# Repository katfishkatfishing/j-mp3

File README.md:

# J-mp3

<h2>Portable Music Player</h2>

<p align="center">
  
</p>
      <p>Making my own portable music player!</p>
      <p>I recently got interested in making my own electronics, and one day, I saw the Teenage Engineering TP7 field recorder. I loved the design it had, and wanted one. But I checked the price and it was wayy too expensive, so I decided to make my own, just only with the audio playing part and without the cool fancy stuff. I'm very new to this, so I couldn't replicate it very well, pls don't be too harsh on my work lol, but please feel free to give me any advice.</p>
      <p>A portable music player inspired by classic iPods, and trying to match the design style of Teenage Engineering, playing audio directly from an inserted microSD card with support for both high-fidelity analog 3.5mm output and Bluetooth audio streaming.</p>
      <p> ⚡Powered by the <strong>ESP32-S31</strong> and PCM5102A Audio DAC</p>
      <p>More projects and revisions coming soon🙏!</p>
      <p>Note: I know the rotary encoder knob is off and too long, but I temporarily have no solutions for that. 💔</p>

## Capabilities
### Microcontroller & Audio
- **ESP32-S31** (ESP32-S31 embedded, RISC-V 32-bit dual-coremicroprocessor, up to 320 MHz, 2.4 GHz Wi-Fi & Bluetooth 5.4 (LE))
- **PCM5102A** Audio Stereo DAC (32-bit, 384kHz high-resolution audio)
- **TDA1308** Class-AB stereo headphone driver amplifier
- **PJ-320B** 3.5mm headphone jack with analog output & Bluetooth audio support

### Display, Controls & Storage
- **1.73" AMOLED Display** (466×466 resolution via high-speed QSPI)
- **EC11E Rotary Encoder** with integrated push button for scroll navigation
- **MicroSD Card Socket** (Hirose DM3AT push-push) for onboard music storage

### Power & Battery Management
- **TP4056** Li-Ion battery charging IC with thermistor temperature sensing
- **DW01A + FS8205A** integrated battery protection (overcharge, overdischarge, overcurrent)
- **TPS2121** Power Multiplexer / Ideal Diode Controller (seamless automatic switching between USB-C and battery)
- **TPS61023** Synchronous boost converter & low-noise **RT9080-33** LDO regulators
- Supports 3.7V LiPo battery (705050 3000mAh)
- USB Type-C receptacle for charging and power input

## J-mp3 PCB
### Schematic

## BOM

| Item | Parts | Qty. | Price per lot (USD) | Source |
| :--- | :--- | :--- | :--- | :--- |
| Audio jack female | PJ-320B | 1 | 3.27 | https://www.aliexpress.com/item/1005010463642476.html?spm=a2g0o.productlist.main.1.60817974ZmbdiL&algo_pvid=3c162c60-ca97-44d8-a4ea-9733957078ac&pdp_ext_f=%7B%22order%22%3A%22106%22%2C%22eval%22%3A%221%22%2C%22fromPage%22%3A%22search%22%7D&utparam-url=scene%3Asearch%7Cquery_from%3A%7Cx_object_id%3A1005010463642476%7C_p_origin_prod%3A |
| Dual N-channel MOSFET | FS8205A | 1 | 1.59 | https://www.aliexpress.com/item/1005006375737459.html?spm=a2g0o.productlist.main.1.a0b04c51uTVtAf&algo_pvid=7da07ac5-ba7f-498b-ae78-000138901bd1&pdp_ext_f=%7B%22order%22%3A%22244%22%2C%22eval%22%3A%221%22%2C%22fromPage%22%3A%22search%22%7D&utparam-url=scene%3Asearch%7Cquery_from%3A%7Cx_object_id%3A1005006375737459%7C_p_origin_prod%3A |
| Ideal Diode Controller | TPS2121RUXR | 1 | 2.09 | https://www.aliexpress.com/item/1005010183114644.html?spm=a2g0o.productlist.main.1.3b79VBZzVBZzNw&algo_pvid=9486a3c5-64df-4774-9556-4dae7f705c93&pdp_ext_f=%7B%22order%22%3A%2224%22%2C%22eval%22%3A%221%22%2C%22fromPage%22%3A%22search%22%7D&utparam-url=scene%3Asearch%7Cquery_from%3A%7Cx_object_id%3A1005010183114644%7C_p_origin_prod%3A |
| ESP32 MCU unit | ESP32-S31-WROOM-3 | 1 | 5.00 | https://www.aliexpress.com/item/1005012434557649.html?invitationCode=aWNUM0JlQUVtMVZjRFJ2NUUzd2xwOVE1RklZQWlQWWxPTmxjTXVvbi9hV2VQemFTZUJrNWVWT0s1MU1hdTAyWg&srcSns=sns_Copy&spreadType=socialShare&social_params=6000474898907&bizType=ProductDetail&spreadCode=aWNUM0JlQUVtMVZjRFJ2NUUzd2xwOVE1RklZQWlQWWxPTmxjTXVvbi9hV2VQemFTZUJrNWVWT0s1MU1hdTAyWg&aff_fcid=838605f6547d4cdc84d85aee383cff12-1789809629059-02194-_c4m7gKM3&tt=MG&aff_fsk=_c4m7gKM3&aff_platform=default&sk=_c4m7gKM3&aff_trace_key=838605f6547d4cdc84d85aee383cff12-1789809629059-02194-_c4m7gKM3&shareId=6000474898907&businessType=ProductDetail&platform=AE&terminal_id=1d9dfb3eef574216a2bcb273506f9cd3&afSmartRedirect=y |
| Boost Voltage Converter | TPS61023DRLR | 1 | 0.18 | https://www.aliexpress.com/item/1005008589999406.html?spm=a2g0o.productlist.main.1.7ed1dAWodAWo0a&algo_pvid=7237dc5c-62cd-42a2-a2e9-dc6ba816f7c3&pdp_ext_f=%7B%22order%22%3A%22302%22%2C%22eval%22%3A%221%22%2C%22fromPage%22%3A%22search%22%7D&utparam-url=scene%3Asearch%7Cquery_from%3A%7Cx_object_id%3A1005008589999406%7C_p_origin_prod%3A |
| Ceramic capacitor SMD | 1uF 0402 | 8 | 2.04 | https://www.aliexpress.com/item/1005012364450156.html?spm=a2g0o.productlist.main.1.589f1Ml51Ml5PA&algo_pvid=64ebbb0e-c998-4523-81f0-ca4e95cd79e7&pdp_ext_f=%7B%22order%22%3A%221484%22%2C%22eval%22%3A%221%22%2C%22fromPage%22%3A%22search%22%7D&utparam-url=scene%3Asearch%7Cquery_from%3A%7Cx_object_id%3A1005012364450156%7C_p_origin_prod%3A |
| P-Channel MOSFET | AO3401A | 1 | 1.99 | https://www.aliexpress.com/item/1005008388291353.html?spm=a2g0o.productlist.main.1.25206b4c4LUtde&algo_pvid=8b50fb0f-e682-4ae7-85c1-8edc45618de3&pdp_ext_f=%7B%22order%22%3A%22692%22%2C%22eval%22%3A%221%22%2C%22fromPage%22%3A%22search%22%7D&utparam-url=scene%3Asearch%7Cquery_from%3A%7Cx_object_id%3A1005008388291353%7C_p_origin_prod%3A |
| Diode | 1N4148 | 2 | 1.97 | https://www.aliexpress.com/item/1005007160563285.html?spm=a2g0o.productlist.main.5.49757952BcmT3Y&algo_pvid=de4616c8-ec89-4be4-9121-617d58f16258&pdp_ext_f=%7B%22order%22%3A%222068%22%2C%22spu_best_type%22%3A%22price%22%2C%22eval%22%3A%221%22%2C%22fromPage%22%3A%22search%22%7D&utparam-url=scene%3Asearch%7Cquery_from%3A%7Cx_object_id%3A1005007160563285%7C_p_origin_prod%3A |
| Audio Stereo DAC | PCM5102A | 1 | 4.46 | https://www.aliexpress.com/item/1005006267865363.html?spm=a2g0o.detail.pcDetailTopMoreOtherSeller.5.308ezYUgzYUgEv&gps-id=pcDetailTopMoreOtherSeller&scm=1007.40050.354490.0&scm_id=1007.40050.354490.0&scm-url=1007.40050.354490.0&pvid=3709ad84-1f45-4f2f-a9d4-9019da4e1276&_t=gps-id%3ApcDetailTopMoreOtherSeller%2Cscm-url%3A1007.40050.354490.0%2Cpvid%3A3709ad84-1f45-4f2f-a9d4-9019da4e1276%2Ctpp_buckets%3A668%232846%238116%232002&pdp_ext_f=%7B%22order%22%3A%2250%22%2C%22eval%22%3A%221%22%2C%22sceneId%22%3A%2230050%22%2C%22fromPage%22%3A%22recommend%22%7D&utparam-url=scene%3ApcDetailTopMoreOtherSeller%7Cquery_from%3A%7Cx_object_id%3A1005006267865363%7C_p_origin_prod%3A |
| Headphone Driver Amplifier | TDA1308 | 1 | 2.08 | https://www.aliexpress.com/item/33051574290.html?spm=a2g0o.productlist.main.16.cf5d7988hDu7CF&algo_pvid=2a75b342-aa82-4fe0-941c-90eca8f2c625&pdp_ext_f=%7B%22order%22%3A%2213%22%2C%22eval%22%3A%221%22%2C%22fromPage%22%3A%22search%22%7D&utparam-url=scene%3Asearch%7Cquery_from%3A%7Cx_object_id%3A33051574290%7C_p_origin_prod%3A |
| Bipolar transistor symbol | NPN SOT-23 | 1 | 5.12 | https://www.aliexpress.com/item/1005012628572946.html?spm=a2g0o.productlist.main.1.1d04e8O1e8O1UQ&algo_pvid=8a51f11c-8b8d-4c0b-af60-1e4180ac1a48&pdp_ext_f=%7B%22order%22%3A%2229%22%2C%22eval%22%3A%221%22%2C%22fromPage%22%3A%22search%22%7D&utparam-url=scene%3Asearch%7Cquery_from%3A%7Cx_object_id%3A1005012628572946%7C_p_origin_prod%3A |
| Generic connector, 02x12 | Conn_02x12_Counter_Clockwise | 1 | 1.50 | https://www.aliexpress.com/item/1005007611939409.html |
| Generic connector, 01x04 | Conn_01x04_Pin | 1 | 1.17 | https://www.aliexpress.com/item/1005012793102722.html?spm=a2g0o.productlist.main.12.573ed4KHd4KHjM&aem_p4p_detail=202609190328541006253439417720000081299&algo_pvid=80c6bcb6-eae0-4a64-9e2c-b5b2595232e3&pdp_ext_f=%7B%22order%22%3A%226%22%2C%22eval%22%3A%221%22%2C%22fromPage%22%3A%22search%22%7D&utparam-url=scene%3Asearch%7Cquery_from%3A%7Cx_object_id%3A1005012793102722%7C_p_origin_prod%3A&search_p4p_id=202609190328541006253439417720000081299_3 |
| Inductor SMD | 2.2uH 0603 | 1 | 2.14 | https://www.aliexpress.com/item/1005004840798951.html?spm=a2g0o.productlist.main.1.4afbESaQESaQvr&algo_pvid=e6f9ad16-910b-43de-9ffc-c876db7ab0df&pdp_ext_f=%7B%22order%22%3A%22359%22%2C%22eval%22%3A%221%22%2C%22fromPage%22%3A%22search%22%7D&utparam-url=scene%3Asearch%7Cquery_from%3A%7Cx_object_id%3A1005004840798951%7C_p_origin_prod%3A |
| Linear Voltage Regulator | RT9080-33GJ5 | 2 | 1.53 | https://www.aliexpress.com/item/1005004159688937.html?spm=a2g0o.productlist.main.1.51784d72rSYVqB&algo_pvid=080971bf-6546-4391-82a5-f72f196448dc&pdp_ext_f=%7B%22order%22%3A%2266%22%2C%22eval%22%3A%221%22%2C%22fromPage%22%3A%22search%22%7D&utparam-url=scene%3Asearch%7Cquery_from%3A%7Cx_object_id%3A1005004159688937%7C_p_origin_prod%3A |
| Micro SD Card Socket | Hirose DM3AT-SF-PEJM5 | 1 | 1.20 | https://www.aliexpress.com/item/1005008529231123.html?spm=a2g0o.productlist.main.15.780faIWTaIWTP1&algo_pvid=3f337965-ee0b-478d-a7b6-a5af69d736c1&pdp_ext_f=%7B%22order%22%3A%2225%22%2C%22eval%22%3A%221%22%2C%22fromPage%22%3A%22search%22%7D&utparam-url=scene%3Asearch%7Cquery_from%3A%7Cx_object_id%3A1005008529231123%7C_p_origin_prod%3A |
| Battery protection | DW01A | 1 | 2.54 | https://www.aliexpress.com/item/1005008626342372.html?spm=a2g0o.productlist.main.1.50895bfdtbnlKJ&algo_pvid=237b56ff-402d-4134-ad38-9a508b1e9970&pdp_ext_f=%7B%22order%22%3A%2270%22%2C%22eval%22%3A%221%22%2C%22fromPage%22%3A%22search%22%7D&utparam-url=scene%3Asearch%7Cquery_from%3A%7Cx_object_id%3A1005008626342372%7C_p_origin_prod%3A |
| Capacitor Tantalum SMD | 100uF 3528-12 (Metric) | 1 | 4.05 | https://my.mouser.com/en/ProductDetail/Vishay-Sprague/293D107X9004B2TE3?qs=N31o%252Bt096guiYtrI%2FhDC5g%3D%3D |
| Capacitor Tantalum SMD | 10uF 0603 | 4 | 9.68 | https://www.aliexpress.com/item/1005003344584575.html?spm=a2g0o.productlist.main.1.7884v2Zuv2ZurL&algo_pvid=d34dac6c-7fb3-48c0-9352-0cc876b7f408&pdp_ext_f=%7B%22order%22%3A%2242%22%2C%22eval%22%3A%221%22%2C%22fromPage%22%3A%22search%22%7D&utparam-url=scene%3Asearch%7Cquery_from%3A%7Cx_object_id%3A1005003344584575%7C_p_origin_prod%3A |
| Push button switch | SW-SMD_TC-1101V-C-B-W | 1 | 0.40 | https://item.szlcsc.com/300030.html |
| Push button switch SMD | SW_SPST_B3U-1000P | 2 | 1.46 | https://www.aliexpress.com/item/1005009548875400.html?spm=a2g0o.productlist.main.1.56ebP1y3P1y3Yd&algo_pvid=e205a10a-479c-4a7d-81eb-9951e2930e82&pdp_ext_f=%7B%22order%22%3A%223%22%2C%22eval%22%3A%221%22%2C%22fromPage%22%3A%22search%22%7D&utparam-url=scene%3Asearch%7Cquery_from%3A%7Cx_object_id%3A1005009548875400%7C_p_origin_prod%3A |
| Ceramic resistor SMD | 10k 0805 | 13 | 1.99 | https://www.aliexpress.com/item/1005007183002569.html?spm=a2g0o.productlist.main.1.68b66b95isN6aN&algo_pvid=385a7354-aa7a-4e7f-8ef9-8c0311d953be&pdp_ext_f=%7B%22order%22%3A%2276%22%2C%22eval%22%3A%221%22%2C%22fromPage%22%3A%22search%22%7D&utparam-url=scene%3Asearch%7Cquery_from%3A%7Cx_object_id%3A1005007183002569%7C_p_origin_prod%3A |
| Ceramic resistor SMD | 2k 0603 | 1 | 1.80 | https://www.aliexpress.com/item/1005003529112557.html?spm=a2g0o.productlist.main.7.4aee65557cxcrB&algo_pvid=0d3dc69f-c884-4762-8069-30f583ccfdb1&pdp_ext_f=%7B%22order%22%3A%22476%22%2C%22spu_best_type%22%3A%22price%22%2C%22eval%22%3A%221%22%2C%22fromPage%22%3A%22search%22%7D&utparam-url=scene%3Asearch%7Cquery_from%3A%7Cx_object_id%3A1005003529112557%7C_p_origin_prod%3A |
| Ceramic resistor SMD | 82k 0805 | 1 | 2.03 | https://www.aliexpress.com/item/1005007183002569.html?spm=a2g0o.productlist.main.1.68b66b95isN6aN&algo_pvid=385a7354-aa7a-4e7f-8ef9-8c0311d953be&pdp_ext_f=%7B%22order%22%3A%2276%22%2C%22eval%22%3A%221%22%2C%22fromPage%22%3A%22search%22%7D&utparam-url=scene%3Asearch%7Cquery_from%3A%7Cx_object_id%3A1005007183002569%7C_p_origin_prod%3A |
| Ceramic resistor SMD | 100 0402 | 1 | 1.38 | https://www.aliexpress.com/item/1005003721873929.html?spm=a2g0o.productlist.main.1.29821u3H1u3HkD&algo_pvid=0c4eed70-6ca0-4e08-b34a-7ee8ebfe2859&pdp_ext_f=%7B%22order%22%3A%22285%22%2C%22eval%22%3A%221%22%2C%22fromPage%22%3A%22search%22%7D&utparam-url=scene%3Asearch%7Cquery_from%3A%7Cx_object_id%3A1005003721873929%7C_p_origin_prod%3A |
| Ceramic resistor SMD | 3.9k 0402 | 4 | 1.38 | https://www.aliexpress.com/item/1005003721873929.html?spm=a2g0o.productlist.main.1.29821u3H1u3HkD&algo_pvid=0c4eed70-6ca0-4e08-b34a-7ee8ebfe2859&pdp_ext_f=%7B%22order%22%3A%22285%22%2C%22eval%22%3A%221%22%2C%22fromPage%22%3A%22search%22%7D&utparam-url=scene%3Asearch%7Cquery_from%3A%7Cx_object_id%3A1005003721873929%7C_p_origin_prod%3A |
| Ceramic resistor SMD | 1m 0603 | 1 | 1.48 | https://www.aliexpress.com/item/1005010109041806.html?spm=a2g0o.productlist.main.1.4a12d8mrd8mrat&algo_pvid=af229fc5-fa32-4342-b395-68c0d5cc9c78&pdp_ext_f=%7B%22order%22%3A%22328%22%2C%22spu_best_type%22%3A%22price%22%2C%22eval%22%3A%221%22%2C%22fromPage%22%3A%22search%22%7D&utparam-url=scene%3Asearch%7Cquery_from%3A%7Cx_object_id%3A1005010109041806%7C_p_origin_prod%3A |
| Ceramic resistor SMD | 5k1 0603 | 2 | 1.75 | https://www.aliexpress.com/item/1005003529112557.html?spm=a2g0o.productlist.main.7.4aee65557cxcrB&algo_pvid=0d3dc69f-c884-4762-8069-30f583ccfdb1&pdp_ext_f=%7B%22order%22%3A%22476%22%2C%22spu_best_type%22%3A%22price%22%2C%22eval%22%3A%221%22%2C%22fromPage%22%3A%22search%22%7D&utparam-url=scene%3Asearch%7Cquery_from%3A%7Cx_object_id%3A1005003529112557%7C_p_origin_prod%3A |
| Ceramic resistor SMD | 1k 0402 | 1 | 1.38 | https://www.aliexpress.com/item/1005003721873929.html?spm=a2g0o.productlist.main.1.29821u3H1u3HkD&algo_pvid=0c4eed70-6ca0-4e08-b34a-7ee8ebfe2859&pdp_ext_f=%7B%22order%22%3A%22285%22%2C%22eval%22%3A%221%22%2C%22fromPage%22%3A%22search%22%7D&utparam-url=scene%3Asearch%7Cquery_from%3A%7Cx_object_id%3A1005003721873929%7C_p_origin_prod%3A |
| Ceramic resistor SMD | 100k 0805 | 6 | 2.00 | https://www.aliexpress.com/item/1005007183002569.html?spm=a2g0o.productlist.main.1.68b66b95isN6aN&algo_pvid=385a7354-aa7a-4e7f-8ef9-8c0311d953be&pdp_ext_f=%7B%22order%22%3A%2276%22%2C%22eval%22%3A%221%22%2C%22fromPage%22%3A%22search%22%7D&utparam-url=scene%3Asearch%7Cquery_from%3A%7Cx_object_id%3A1005007183002569%7C_p_origin_prod%3A |
| Ceramic resistor SMD | 4.7k 0805 | 1 | 2.00 | https://www.aliexpress.com/item/1005007183002569.html?spm=a2g0o.productlist.main.1.68b66b95isN6aN&algo_pvid=385a7354-aa7a-4e7f-8ef9-8c0311d953be&pdp_ext_f=%7B%22order%22%3A%2276%22%2C%22eval%22%3A%221%22%2C%22fromPage%22%3A%22search%22%7D&utparam-url=scene%3Asearch%7Cquery_from%3A%7Cx_object_id%3A1005007183002569%7C_p_origin_prod%3A |
| Ceramic resistor SMD | 470 0603 | 2 | 1.80 | https://www.aliexpress.com/item/1005003529112557.html?spm=a2g0o.productlist.main.7.4aee65557cxcrB&algo_pvid=0d3dc69f-c884-4762-8069-30f583ccfdb1&pdp_ext_f=%7B%22order%22%3A%22476%22%2C%22spu_best_type%22%3A%22price%22%2C%22eval%22%3A%221%22%2C%22fromPage%22%3A%22search%22%7D&utparam-url=scene%3Asearch%7Cquery_from%3A%7Cx_object_id%3A1005003529112557%7C_p_origin_prod%3A |
| Ceramic resistor SMD | 43k 0805 | 1 | 2.03 | https://www.aliexpress.com/item/1005007183002569.html?spm=a2g0o.productlist.main.1.68b66b95isN6aN&algo_pvid=385a7354-aa7a-4e7f-8ef9-8c0311d953be&pdp_ext_f=%7B%22order%22%3A%2276%22%2C%22eval%22%3A%221%22%2C%22fromPage%22%3A%22search%22%7D&utparam-url=scene%3Asearch%7Cquery_from%3A%7Cx_object_id%3A1005007183002569%7C_p_origin_prod%3A |
| Ceramic resistor SMD | 732k 0603 | 1 | 2.10 | https://www.aliexpress.com/item/1005005459557840.html?spm=a2g0o.productlist.main.1.552eKaoZKaoZOW&algo_pvid=d5c5bb48-d381-4227-ba1e-46e8d7582c70&pdp_ext_f=%7B%22order%22%3A%2277%22%2C%22eval%22%3A%221%22%2C%22fromPage%22%3A%22search%22%7D&utparam-url=scene%3Asearch%7Cquery_from%3A%7Cx_object_id%3A1005005459557840%7C_p_origin_prod%3A |
| Rotary encoder with switch | EC11E | 1 | 2.94 | https://www.aliexpress.com/item/32976046900.html?spm=a2g0o.detail.pcDetailBottomMoreOtherSeller.13.6474lV6ElV6Evn&gps-id=pcDetailBottomMoreOtherSeller&scm=1007.14452.396806.0&scm_id=1007.14452.396806.0&scm-url=1007.14452.396806.0&pvid=aeb64c1f-7a29-4ad5-933b-e98472c40c59&_t=gps-id%3ApcDetailBottomMoreOtherSeller%2Cscm-url%3A1007.14452.396806.0%2Cpvid%3Aaeb64c1f-7a29-4ad5-933b-e98472c40c59%2Ctpp_buckets%3A668%232846%238116%232002&pdp_ext_f=%7B%22order%22%3A%22547%22%2C%22eval%22%3A%221%22%2C%22sceneId%22%3A%2230050%22%2C%22fromPage%22%3A%22recommend%22%7D&utparam-url=scene%3ApcDetailBottomMoreOtherSeller%7Cquery_from%3A%7Cx_object_id%3A32976046900%7C_p_origin_prod%3A&search_p4p_id=202608180535232983463426697065023539_2 |
| Single-cell battery | 755060 LiPo 3000mAh | 1 | 8.90 | https://www.aliexpress.com/item/1005006259194674.html?spm=a2g0o.productlist.main.2.36fb5dcS5dcSS8&algo_pvid=e5418aaa-c7d1-42cf-949d-d8510645f5cd&pdp_ext_f=%7B%22order%22%3A%22151%22%2C%22eval%22%3A%221%22%2C%22fromPage%22%3A%22search%22%7D&utparam-url=scene%3Asearch%7Cquery_from%3A%7Cx_object_id%3A1005006259194674%7C_p_origin_prod%3A |
| Li-lon Battery Charger | TP4056 | 1 | 0.52 | https://www.aliexpress.com/item/1005005487915175.html?spm=a2g0o.productlist.main.8.4b6058c9uwNrRB&aem_p4p_detail=202609190258166749914128201200000080084&algo_pvid=0f66a318-1b84-45cd-80d0-95d22f5eb897&pdp_ext_f=%7B%22order%22%3A%22255%22%2C%22eval%22%3A%221%22%2C%22fromPage%22%3A%22search%22%7D&utparam-url=scene%3Asearch%7Cquery_from%3A%7Cx_object_id%3A1005005487915175%7C_p_origin_prod%3A&search_p4p_id=202609190258166749914128201200000080084_2 |
| Thermistor | 10k 0402 | 1 | 2.81 | https://www.aliexpress.com/item/1005010466857933.html?spm=a2g0o.productlist.main.2.4fb8w7gbw7gbc4&algo_pvid=0c2c7f04-0061-4f44-94c4-1ea901b197c0&pdp_ext_f=%7B%22order%22%3A%2228%22%2C%22eval%22%3A%221%22%2C%22fromPage%22%3A%22search%22%7D&utparam-url=scene%3Asearch%7Cquery_from%3A%7Cx_object_id%3A1005010466857933%7C_p_origin_prod%3A |
| Ceramic capacitor SMD | 100nF 0603 | 4 | 2.01 | https://www.aliexpress.com/item/1005007660078779.html?spm=a2g0o.productlist.main.1.41ad17afXggjid&algo_pvid=94b82144-0913-4272-a928-8d27b54f2344&pdp_ext_f=%7B%22order%22%3A%22790%22%2C%22spu_best_type%22%3A%22price%22%2C%22eval%22%3A%221%22%2C%22fromPage%22%3A%22search%22%7D&utparam-url=scene%3Asearch%7Cquery_from%3A%7Cx_object_id%3A1005007660078779%7C_p_origin_prod%3A |
| Ceramic capacitor SMD | 10uF 0805 | 5 | 2.64 | https://www.aliexpress.com/item/1005012364450156.html?spm=a2g0o.productlist.main.1.4a92101aYp6fpR&algo_pvid=def9331d-468c-46b6-a7c2-2492d88f5a7b&pdp_ext_f=%7B%22order%22%3A%221484%22%2C%22eval%22%3A%221%22%2C%22fromPage%22%3A%22search%22%7D&utparam-url=scene%3Asearch%7Cquery_from%3A%7Cx_object_id%3A1005012364450156%7C_p_origin_prod%3A |
| Ceramic capacitor SMD | 1uF 0805 | 3 | 2.35 | https://www.aliexpress.com/item/1005012364450156.html?spm=a2g0o.productlist.main.1.4a92101aYp6fpR&algo_pvid=def9331d-468c-46b6-a7c2-2492d88f5a7b&pdp_ext_f=%7B%22order%22%3A%221484%22%2C%22eval%22%3A%221%22%2C%22fromPage%22%3A%22search%22%7D&utparam-url=scene%3Asearch%7Cquery_from%3A%7Cx_object_id%3A1005012364450156%7C_p_origin_prod%3A |
| Ceramic capacitor SMD | 10nF 0603 | 1 | 2.00 | https://www.aliexpress.com/item/1005007660078779.html?spm=a2g0o.productlist.main.1.41ad17afXggjid&algo_pvid=94b82144-0913-4272-a928-8d27b54f2344&pdp_ext_f=%7B%22order%22%3A%22790%22%2C%22spu_best_type%22%3A%22price%22%2C%22eval%22%3A%221%22%2C%22fromPage%22%3A%22search%22%7D&utparam-url=scene%3Asearch%7Cquery_from%3A%7Cx_object_id%3A1005007660078779%7C_p_origin_prod%3A |
| Ceramic capacitor SMD | 22uF 0805 | 3 | 3.55 | https://www.aliexpress.com/item/1005012364450156.html?spm=a2g0o.productlist.main.1.4a92101aYp6fpR&algo_pvid=def9331d-468c-46b6-a7c2-2492d88f5a7b&pdp_ext_f=%7B%22order%22%3A%221484%22%2C%22eval%22%3A%221%22%2C%22fromPage%22%3A%22search%22%7D&utparam-url=scene%3Asearch%7Cquery_from%3A%7Cx_object_id%3A1005012364450156%7C_p_origin_prod%3A |
| Ceramic capacitor SMD | 0.1uF 0805 | 2 | 1.43 | https://www.aliexpress.com/item/1005006142309480.html?spm=a2g0o.productlist.main.2.5b5d23fbK7Es7i&algo_pvid=b69da919-24fd-4e5c-b25c-abccb2827b6a&pdp_ext_f=%7B%22order%22%3A%226337%22%2C%22spu_best_type%22%3A%22price%22%2C%22eval%22%3A%221%22%2C%22fromPage%22%3A%22search%22%7D&utparam-url=scene%3Asearch%7Cquery_from%3A%7Cx_object_id%3A1005006142309480%7C_p_origin_prod%3A |
| Ceramic capacitor SMD | 100uF 0805 | 2 | 13.72 | https://www.aliexpress.com/item/1005005590636993.html?spm=a2g0o.productlist.main.2.258950300kp4f9&algo_pvid=b9072869-1443-4f9f-9d83-403e7e57091f&pdp_ext_f=%7B%22order%22%3A%22357%22%2C%22spu_best_type%22%3A%22price%22%2C%22eval%22%3A%221%22%2C%22fromPage%22%3A%22search%22%7D&utparam-url=scene%3Asearch%7Cquery_from%3A%7Cx_object_id%3A1005005590636993%7C_p_origin_prod%3A |
| Ceramic capacitor SMD | 0.1uF 0201 | 4 | 0.95 | https://www.aliexpress.com/item/1005008499718166.html?spm=a2g0o.productlist.main.3.4f072457BLp6JC&algo_pvid=708b6ba6-6d07-40b3-8c9c-719163e04cda&pdp_ext_f=%7B%22order%22%3A%22397%22%2C%22eval%22%3A%221%22%2C%22fromPage%22%3A%22search%22%7D&utparam-url=scene%3Asearch%7Cquery_from%3A%7Cx_object_id%3A1005008499718166%7C_p_origin_prod%3A |
| Ceramic capacitor SMD | 2.2uF 0603 | 2 | 2.03 | https://www.aliexpress.com/item/1005007660078779.html?spm=a2g0o.productlist.main.1.41ad17afXggjid&algo_pvid=94b82144-0913-4272-a928-8d27b54f2344&pdp_ext_f=%7B%22order%22%3A%22790%22%2C%22spu_best_type%22%3A%22price%22%2C%22eval%22%3A%221%22%2C%22fromPage%22%3A%22search%22%7D&utparam-url=scene%3Asearch%7Cquery_from%3A%7Cx_object_id%3A1005007660078779%7C_p_origin_prod%3A |
| Ceramic capacitor SMD | 1nF 0603 | 1 | 1.98 | https://www.aliexpress.com/item/1005007660078779.html?spm=a2g0o.productlist.main.1.41ad17afXggjid&algo_pvid=94b82144-0913-4272-a928-8d27b54f2344&pdp_ext_f=%7B%22order%22%3A%22790%22%2C%22spu_best_type%22%3A%22price%22%2C%22eval%22%3A%221%22%2C%22fromPage%22%3A%22search%22%7D&utparam-url=scene%3Asearch%7Cquery_from%3A%7Cx_object_id%3A1005007660078779%7C_p_origin_prod%3A |
| Ceramic capacitor SMD | 2.2nF 0805 | 2 | 3.04 | https://www.aliexpress.com/item/33039604868.html?spm=a2g0o.productlist.main.10.3afdzjnrzjnr3Q&algo_pvid=66e61c7f-f79e-40bc-bf5d-0d52052e1876&pdp_ext_f=%7B%22order%22%3A%2258%22%2C%22eval%22%3A%221%22%2C%22fromPage%22%3A%22search%22%7D&utparam-url=scene%3Asearch%7Cquery_from%3A%7Cx_object_id%3A33039604868%7C_p_origin_prod%3A |
| Ceramic capacitor SMD | 100pF 0603 | 1 | 2.03 | https://www.aliexpress.com/item/1005007660078779.html?spm=a2g0o.productlist.main.1.1729LAMPLAMPww&algo_pvid=134453e7-f153-4dc4-9327-eebe4236be4f&pdp_ext_f=%7B%22order%22%3A%22790%22%2C%22spu_best_type%22%3A%22price%22%2C%22eval%22%3A%221%22%2C%22fromPage%22%3A%22search%22%7D&utparam-url=scene%3Asearch%7Cquery_from%3A%7Cx_object_id%3A1005007660078779%7C_p_origin_prod%3A |
| USBType-C Receptacle | USB4125-GF-A | 1 | 0.60 | https://www.digikey.my/en/products/detail/gct/USB4125-GF-A/13547388 |
| AMOLED Display | 1.73 inch 466x466 QSPI | 1 | 7.47 | https://item.taobao.com/item.htm?id=952177467095&mi_id=0000jOy7u6r5ZkyFyRkc3t68ZxdEMGvtNs0QXCuW6-oULvo&spm=a21xtw.29178619.0.0&xxc=shop |
| Total+Shipping+Tax | - | - | 139.55± | - |

### Footprint
<table>
  <tr>
    <td>
      
    </td>
    <td>
      
    </td>
  </tr>
  <tr>
    <td>
      
    </td>
    <td>
      
    </td>
  </tr>
</table>

### 3D View
<table>
  <tr>
    <td>
      
    </td>
    <td>
      
    </td>
  </tr>
  <tr>
    <td>
      
    </td>
    <td>
      
    </td>
  </tr>
  <tr>
    <td>
      
    </td>
    <td>
      
    </td>
  </tr>
</table>

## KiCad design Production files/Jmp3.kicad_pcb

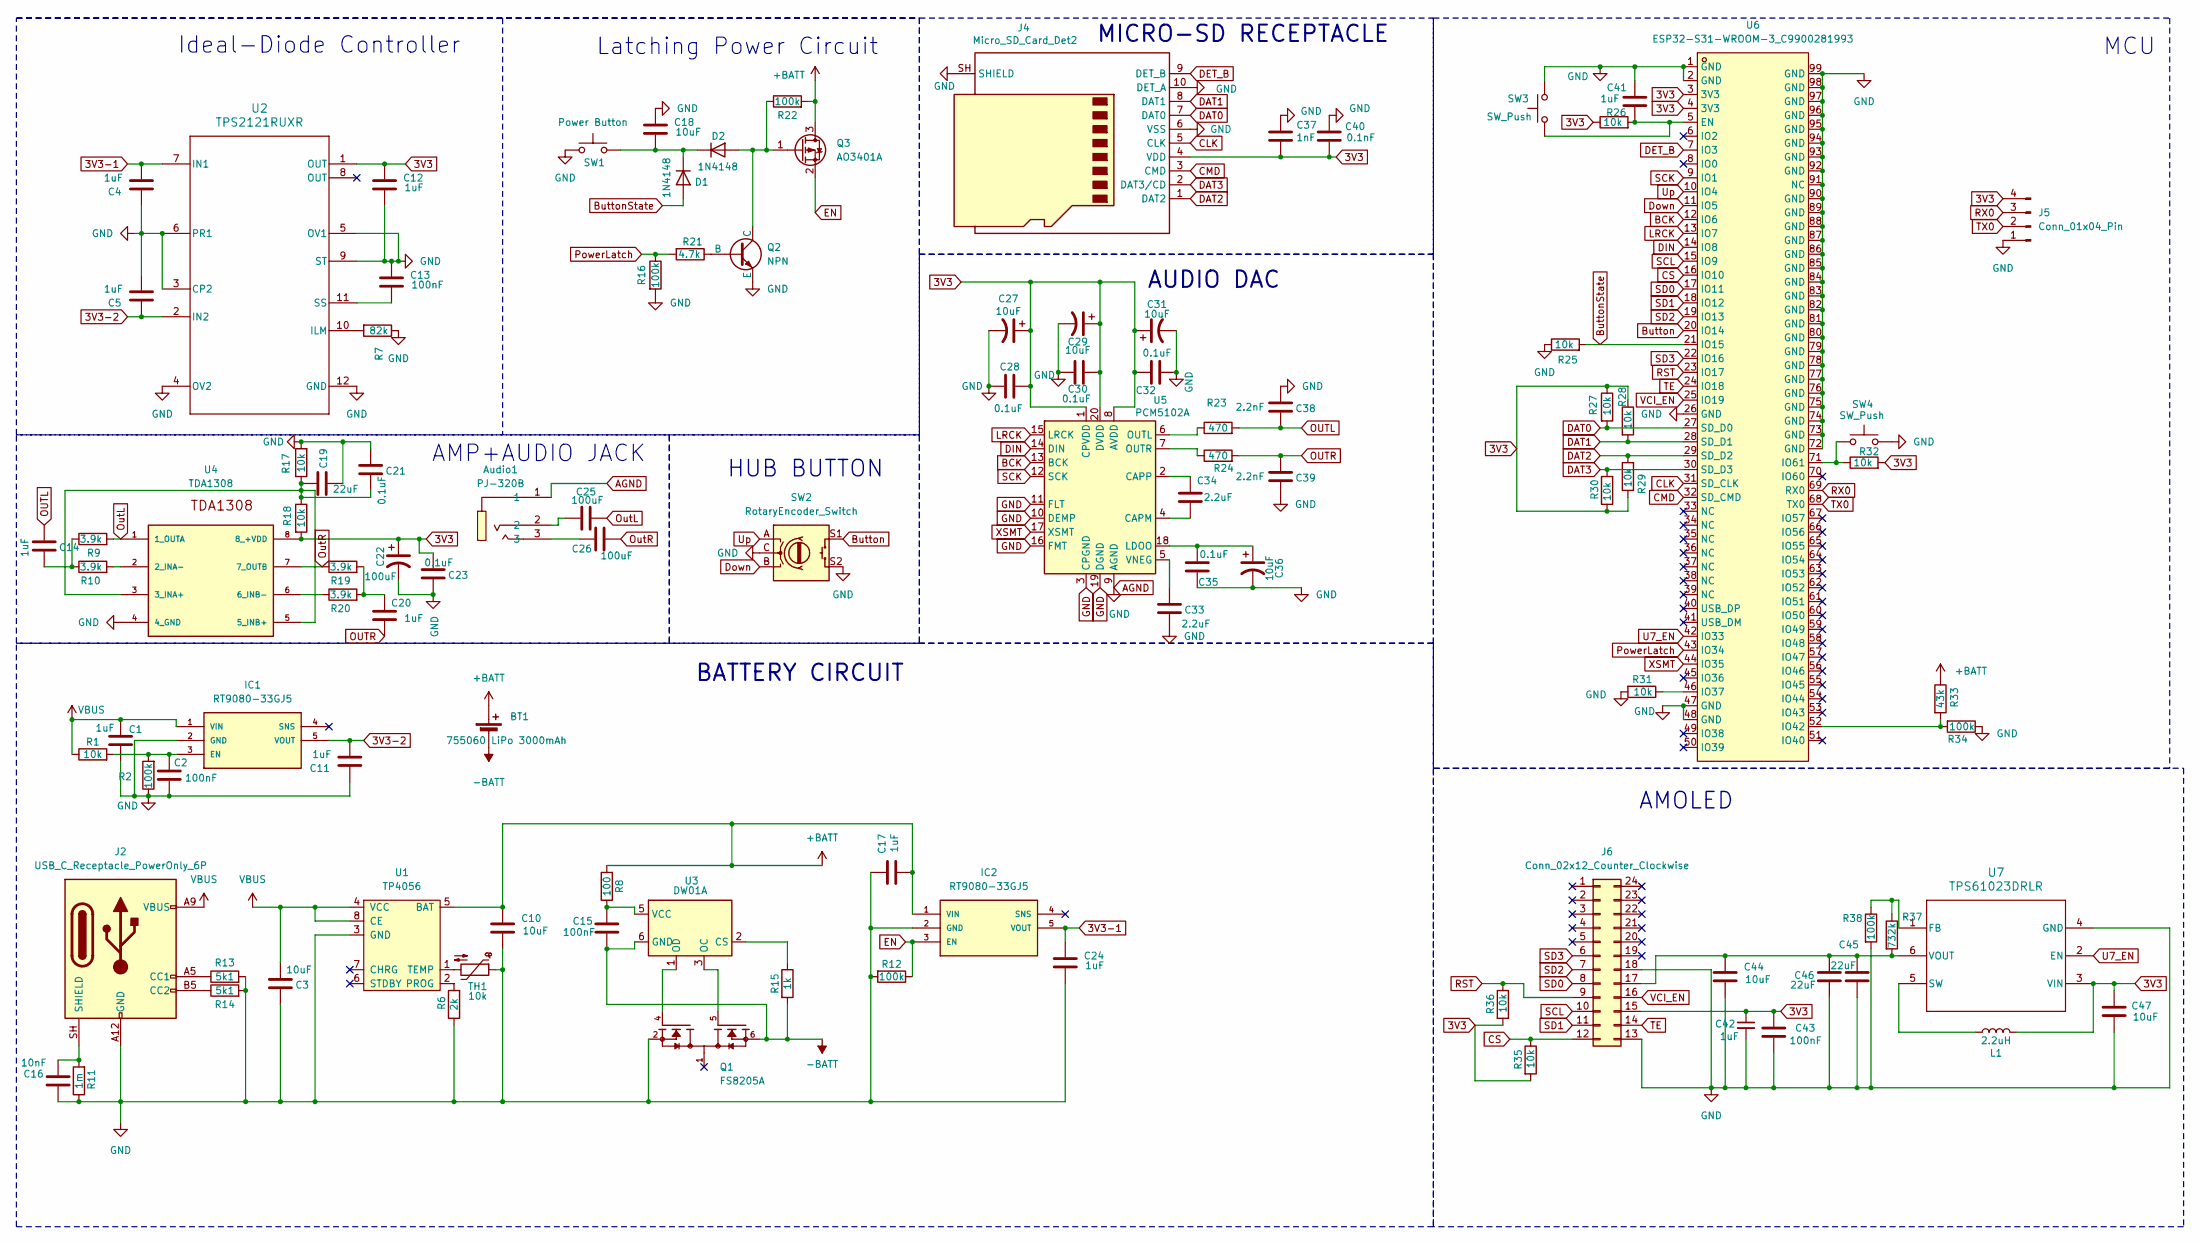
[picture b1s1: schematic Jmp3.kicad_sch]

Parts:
Audio1: PJ-320B; AUDIO-SMD_PJ-320B_C2884998; MPN PJ-320B贴片; LCSC Part C18594
BT1: 755060 LiPo 3000mAh; JST_EH_S2B-EH_1x02_P2.50mm_Horizontal
C1, C4, C5, C11, C12, C17, C24, C42: 1uF; C_0402_1005Metric_Pad0.74x0.62mm_HandSolder
C2, C13, C15, C43: 100nF; C_0603_1608Metric_Pad1.08x0.95mm_HandSolder
C3, C10, C18, C44, C47: 10uF; C_0805_2012Metric_Pad1.18x1.45mm_HandSolder
C14, C20, C41: 1uF; C_0805_2012Metric_Pad1.18x1.45mm_HandSolder
C16: 10nF; C_0603_1608Metric_Pad1.08x0.95mm_HandSolder
C19, C45, C46: 22uF; C_0805_2012Metric_Pad1.18x1.45mm_HandSolder
C21, C23: 0.1uF; C_0805_2012Metric_Pad1.18x1.45mm_HandSolder
C22: 100uF; CP_EIA-3528-12_Kemet-T_HandSolder
C25, C26: 100uF; C_0805_2012Metric_Pad1.18x1.45mm_HandSolder
C27, C29, C31, C36: 10uF; C_0603_1608Metric_Pad1.08x0.95mm_HandSolder
C28, C30, C32, C35: 0.1uF; C_0201_0603Metric_Pad0.64x0.40mm_HandSolder
C33, C34: 2.2uF; C_0603_1608Metric_Pad1.08x0.95mm_HandSolder
C37: 1nF; C_0603_1608Metric_Pad1.08x0.95mm_HandSolder
C38, C39: 2.2nF; C_0805_2012Metric_Pad1.18x1.45mm_HandSolder
C40: 0.1nF; C_0603_1608Metric_Pad1.08x0.95mm_HandSolder
D1, D2: 1N4148; D_SOD-323
IC1, IC2: RT9080-33GJ5; SOT94P280X100-5N
J2: USB_C_Receptacle_PowerOnly_6P; USB_C_Receptacle_GCT_USB4125-xx-x-0190_6P_TopMnt_Horizontal
J4: Micro_SD_Card_Det2; microSD_HC_Hirose_DM3AT-SF-PEJM5
J5: Conn_01x04_Pin; PinHeader_1x04_P1.00mm_Horizontal
J6: Conn_02x12_Counter_Clockwise; CONN-SMD_OK-23GM024-04
L1: 2.2uH; L_0603_1608Metric_Pad1.05x0.95mm_HandSolder
Q1: FS8205A; SOP65P640X120-8N; PARTREV 1.7
Q2: NPN; Q_SOT-23
Q3: AO3401A; SOT-23
R1, R17, R18, R25, R26, R27, R28, R29, R30, R31, R32, R35, R36: 10k; R_0805_2012Metric_Pad1.20x1.40mm_HandSolder
R2, R12, R16, R22, R34, R38: 100k; R_0805_2012Metric_Pad1.20x1.40mm_HandSolder
R6: 2k; R_0603_1608Metric_Pad0.98x0.95mm_HandSolder
R7: 82k; R_0805_2012Metric_Pad1.20x1.40mm_HandSolder
R8: 100; R_0402_1005Metric_Pad0.72x0.64mm_HandSolder
R9, R10, R19, R20: 3.9k; R_0402_1005Metric_Pad0.72x0.64mm_HandSolder
R11: 1m; R_0603_1608Metric_Pad0.98x0.95mm_HandSolder
R13, R14: 5k1; R_0603_1608Metric_Pad0.98x0.95mm_HandSolder
R15: 1k; R_0402_1005Metric_Pad0.72x0.64mm_HandSolder
R21: 4.7k; R_0805_2012Metric_Pad1.20x1.40mm_HandSolder
R23, R24: 470; R_0603_1608Metric_Pad0.98x0.95mm_HandSolder
R33: 43k; R_0805_2012Metric_Pad1.20x1.40mm_HandSolder
R37: 732k; R_0603_1608Metric_Pad0.98x0.95mm_HandSolder
SW1: Power Button; SW-SMD_TC-1101V-C-B-W
SW2: RotaryEncoder_Switch; RotaryEncoder_Alps_EC11E-Switch_Vertical_H20mm
SW3, SW4: SW_Push; SW_SPST_B3U-1000P
TH1: 10k; THERM_NTCG103JF103FT1
U1: TP4056; SOP-8-1EP_4.57x4.57mm_P1.27mm_EP4.57x4.45mm; LCSC C16581
U2: TPS2121RUXR; RUX0012A
U3: DW01A; SOT-23-6
U4: TDA1308; SO8
U5: PCM5102A; TSSOP-20_4.4x6.5mm_P0.65mm
U6: ESP32-S31-WROOM-3_C9900281993; esp32s31wroom3; MPN ESP32-S31-WROOM-3; LCSC Part C9900281993
U7: TPS61023DRLR; DRL0006A

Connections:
3V3: C12.1, C22.1, C23.1, C27.1, C28.2, C29.1, C30.2, C31.1, C32.2, C37.2, C40.2, C42.1, C43.1, C47.1, J4.4 (VDD), J5.4, J6.15, L1.2, R18.2, R26.1, R27.1, R28.1, R29.1, R30.1, R32.2, R35.2, R36.2, U2.1 (OUT), U4.8 (8_+VDD), U5.1 (CPVDD), U5.8 (AVDD), U5.20 (DVDD), U6.3 (3V3), U6.4 (3V3), U7.3 (VIN)
3V3-1: C4.2, C24.1, IC2.5 (VOUT), U2.7 (IN1)
3V3-2: C5.1, C11.2, IC1.5 (VOUT), U2.2 (IN2)
+BATT: BT1.1 (+), C10.1, C17.2, IC2.1 (VIN), Q3.3 (D), R8.2, R22.2, R33.1, U1.5 (BAT)
-BATT: BT1.2 (-), C15.2, Q1.6, Q1.7, R15.2, U3.6 (GND)
AGND: Audio1.1, C1.1, C2.2, C3.1, C4.1, C5.2, C10.2, C11.1, C12.2, C13.1, C16.1, C17.1, C18.1, C19.2, C21.1, C22.2, C23.2, C24.2, C27.2, C28.1, C29.2, C30.1, C31.2, C32.1, C33.2, C35.2, C36.2, C37.1, C38.1, C39.2, C40.1, C41.2, C42.2, C43.2, C44.2, C45.1, C46.1, C47.2, IC1.2 (GND), IC2.2 (GND), J2.A12 (GND), J2.B12 (GND), J4.6 (VSS), J4.10 (DET_A), J4.SH (SHIELD), J5.1, J6.13, J6.18, Q1.2, Q1.3, Q2.3 (E), R2.1, R6.1, R7.1, R11.1, R12.2, R13.2, R14.2, R16.2, R17.2, R25.1, R31.2, R34.1, R38.2, SW1.1, SW2.C, SW2.S2, SW3.2, SW4.2, TH1.1, U1.3 (GND), U2.3 (CP2), U2.4 (OV2), U2.5 (OV1), U2.6 (PR1), U2.9 (ST), U2.12 (GND), U4.4 (4_GND), U5.3 (CPGND), U5.9 (AGND), U5.10 (DEMP), U5.11 (FLT), U5.16 (FMT), U5.19 (DGND), U6.1 (GND), U6.2 (GND), U6.26 (GND), U6.47 (GND), U6.48 (GND), U6.72 (GND), U6.73 (GND), U6.74 (GND), U6.75 (GND), U6.76 (GND), U6.77 (GND), U6.78 (GND), U6.79 (GND), U6.80 (GND), U6.81 (GND), U6.82 (GND), U6.83 (GND), U6.84 (GND), U6.85 (GND), U6.86 (GND), U6.87 (GND), U6.88 (GND), U6.89 (GND), U6.90 (GND), U6.91 (NC), U6.92 (GND), U6.93 (GND), U6.94 (GND), U6.95 (GND), U6.96 (GND), U6.97 (GND), U6.98 (GND), U6.99 (GND), U7.4 (GND)
BCK: U5.13 (BCK), U6.12 (IO6)
Button: SW2.S1, U6.20 (IO14)
ButtonState: D1.2 (A), R25.2, U6.21 (IO15)
CLK: J4.5 (CLK), U6.31 (SD_CLK)
CMD: J4.3 (CMD), U6.32 (SD_CMD)
CS: J6.12, R35.1, U6.16 (IO10)
DAT0: J4.7 (DAT0), R27.2, U6.27 (SD_D0)
DAT1: J4.8 (DAT1), R28.2, U6.28 (SD_D1)
DAT2: J4.1 (DAT2), R29.2, U6.29 (SD_D2)
DAT3: J4.2 (DAT3/CD), R30.2, U6.30 (SD_D3)
DET_B: J4.9 (DET_B), U6.7 (IO3)
DIN: U5.14 (DIN), U6.14 (IO8)
Down: SW2.B, U6.11 (IO5)
EN: IC2.3 (EN), Q3.2 (S), R12.1
LRCK: U5.15 (LRCK), U6.13 (IO7)
unnamed: Audio1.2, C25.2
unnamed: Audio1.3, C26.1
unnamed: C14.2, R9.1, R10.1
unnamed: C20.2, R19.2, R20.2
unnamed: C18.2, D1.1 (K), D2.1 (K), SW1.2
unnamed: D2.2 (A), Q2.1 (C), Q3.1 (G), R22.1
unnamed: C2.1, IC1.3 (EN), R1.2, R2.2
unnamed: J2.A5 (CC1), R13.1
unnamed: J2.B5 (CC2), R14.1
unnamed: C16.2, J2.SH (SHIELD), R11.2
unnamed: C44.1, C45.2, C46.2, J6.17, R37.2, U7.6 (VOUT)
unnamed: Q2.2 (B), R21.1
unnamed: R6.2, U1.2 (PROG)
unnamed: TH1.2, U1.1 (TEMP)
unnamed: R7.2, U2.10 (ILM)
unnamed: C13.2, U2.11 (SS)
unnamed: R15.1, U3.2 (CS)
unnamed: Q1.5, U3.3 (OC)
unnamed: Q1.4, U3.1 (OD)
unnamed: C15.1, R8.1, U3.5 (VCC)
unnamed: R10.2, U4.2 (2_INA-)
unnamed: C19.1, C21.2, R17.1, R18.1, U4.3 (3_INA+), U4.5 (5_INB+)
unnamed: R20.1, U4.6 (6_INB-)
unnamed: C34.1, U5.4 (CAPM)
unnamed: C34.2, U5.2 (CAPP)
unnamed: C35.1, C36.1, U5.18 (LDOO)
unnamed: R23.1, U5.6 (OUTL)
unnamed: R24.1, U5.7 (OUTR)
unnamed: C33.1, U5.5 (VNEG)
unnamed: C41.1, R26.2, SW3.1, U6.5 (EN)
unnamed: R31.1, U6.46 (IO37)
unnamed: R33.2, R34.2, U6.52 (IO42)
unnamed: R32.1, SW4.1, U6.71 (IO61)
unnamed: R37.1, R38.1, U7.1 (FB)
unnamed: L1.1, U7.5 (SW)
OUTL: C14.1, C38.2, R23.2
OUTR: C20.1, C39.1, R24.2
OutL: C25.1, R9.2, U4.1 (1_OUTA)
OutR: C26.2, R19.1, U4.7 (7_OUTB)
PowerLatch: R16.1, R21.2, U6.43 (IO34)
RST: J6.9, R36.1, U6.23 (IO17)
RX0: J5.3, U6.69 (RX0)
SCK: U5.12 (SCK), U6.9 (IO1)
SCL: J6.10, U6.15 (IO9)
SD0: J6.8, U6.17 (IO11)
SD1: J6.11, U6.18 (IO12)
SD2: J6.7, U6.19 (IO13)
SD3: J6.6, U6.22 (IO16)
TE: J6.14, U6.24 (IO18)
TX0: J5.2, U6.68 (TX0)
U7_EN: U6.42 (IO33), U7.2 (EN)
Up: SW2.A, U6.10 (IO4)
VBUS: C1.2, C3.2, IC1.1 (VIN), J2.A9 (VBUS), J2.B9 (VBUS), R1.1, U1.4 (VCC), U1.8 (CE)
VCI_EN: J6.16, U6.25 (IO19)
XSMT: U5.17 (XSMT), U6.44 (IO35)

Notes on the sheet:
Ideal-Diode Controller
BATTERY CIRCUIT
AUDIO DAC
AMP+AUDIO JACK
HUB BUTTON
MICRO-SD RECEPTACLE
MCU
AMOLED
Latching Power Circuit

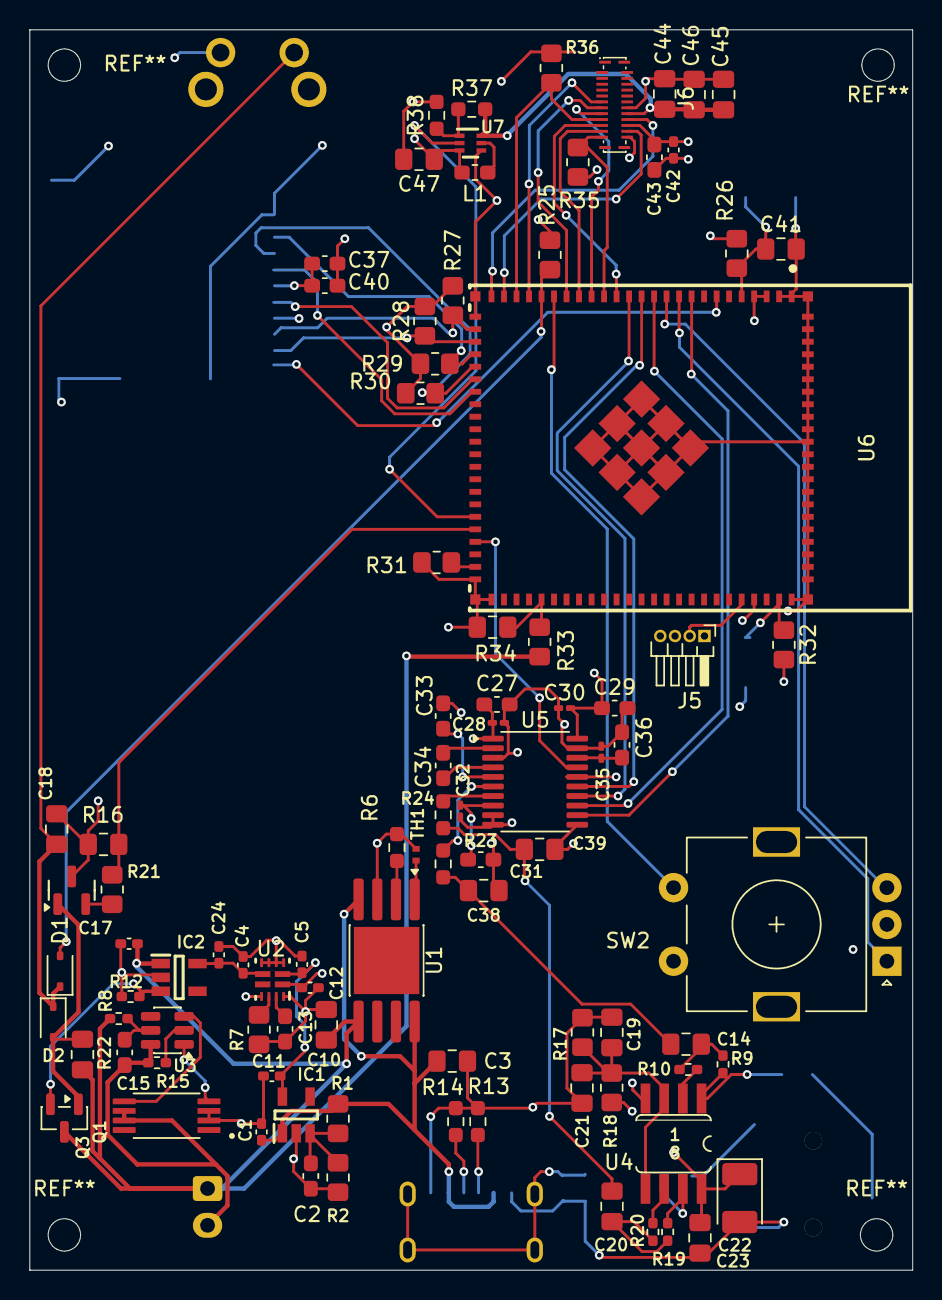
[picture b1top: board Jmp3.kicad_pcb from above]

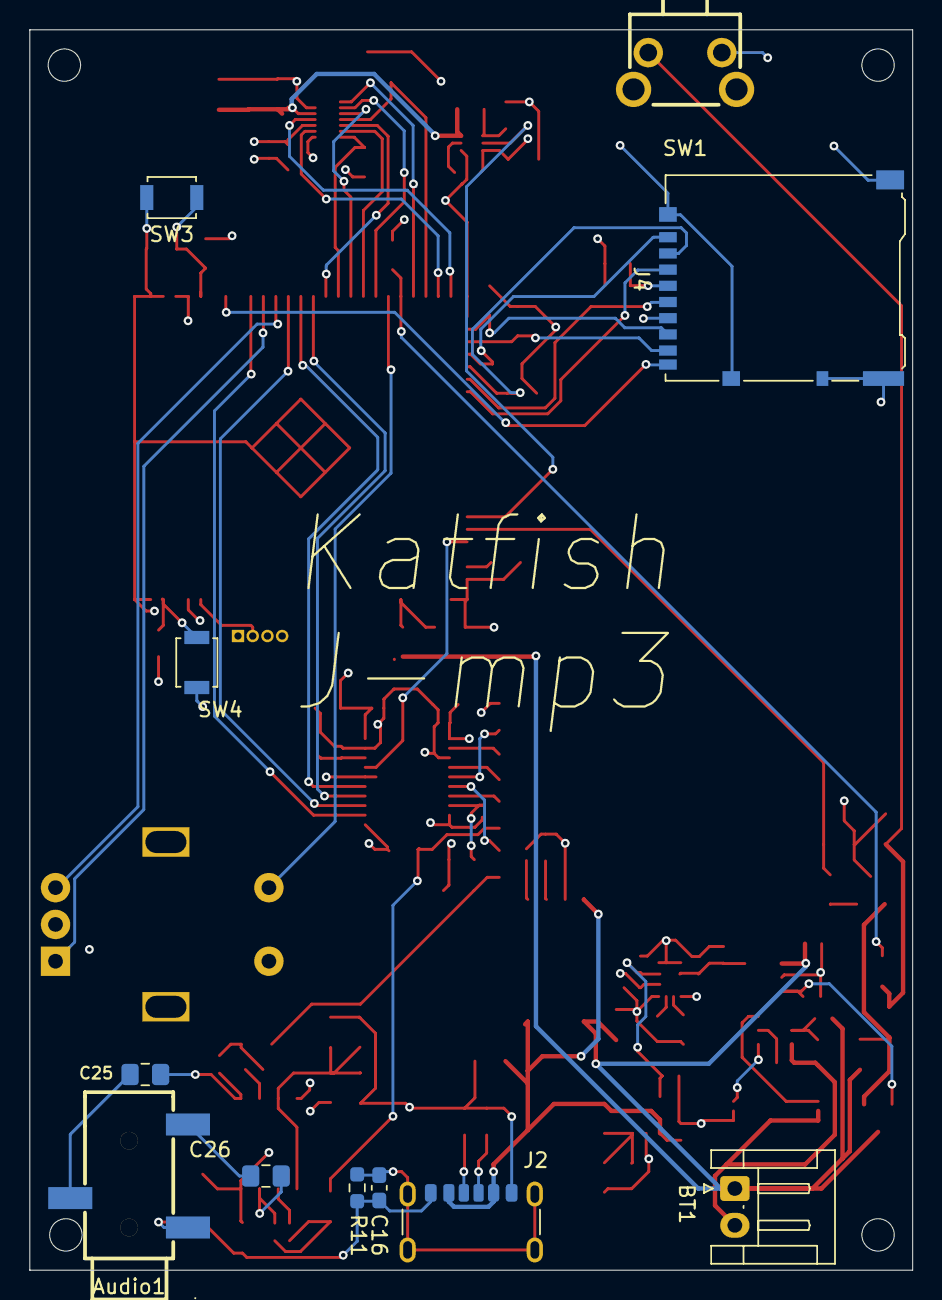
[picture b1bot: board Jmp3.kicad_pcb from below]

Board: 4 copper layers, 60.0 x 84.3 mm, 104 parts (11 on the bottom side), 76 nets.

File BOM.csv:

"Description","Value","Qty","Price per lot(USD)","Source"
"Audio jack female","PJ-320B","1","3.27","https://www.aliexpress.com/item/1005010463642476.html?spm=a2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"
"Dual N-channel MOSFET","FS8205A","1","1.59","https://www.aliexpress.com/item/1005006375737459.html?spm=a2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"
"Ideal Diode Controller","TPS2121RUXR","1","2.09","https://www.aliexpress.com/item/1005010183114644.html?spm=a2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"
"ESP32 MCU unit","ESP32-S31-WROOM-3","1","5.00","https://www.aliexpress.com/item/1005012434557649.html?invita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"
"Boost Voltage Converter","TPS61023DRLR","1","0.18","https://www.aliexpress.com/item/1005008589999406.html?spm=a2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"
"Ceramic capacitor SMD","1uF 0402","8","2.04","https://www.aliexpress.com/item/1005012364450156.html?spm=a2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"
"P-Channel MOSFET","AO3401A","1","1.99","https://www.aliexpress.com/item/1005008388291353.html?spm=a2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"
"Diode","1N4148","2","1.97","https://www.aliexpress.com/item/1005007160563285.html?spm=a2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"
"Audio Stereo DAC","PCM5102A","1","4.46","https://www.aliexpress.com/item/1005006267865363.html?spm=a2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"
"Headphone Driver Amplifier","TDA1308","1","2.08","https://www.aliexpress.com/item/33051574290.html?spm=a2g0o.p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"
"Bipolar transistor symbol","NPN SOT-23","1","5.12","https://www.aliexpress.com/item/1005012628572946.html?spm=a2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"
"Generic connector, 02x12","Conn_02x12_Counter_Clockwise","1","1.50","https://www.aliexpress.com/item/1005007611939409.html"
"Generic connector, 01x04","Conn_01x04_Pin","1","1.17","https://www.aliexpress.com/item/1005012793102722.html?spm=a2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"
"Inductor SMD","2.2uH 0603","1","2.14","https://www.aliexpress.com/item/1005004840798951.html?spm=a2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"
"Linear Voltage Regulator","RT9080-33GJ5","2","1.53","https://www.aliexpress.com/item/1005004159688937.html?spm=a2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"
"Micro SD Card Socket","Hirose DM3AT-SF-PEJM5","1","1.20 ","https://www.aliexpress.com/item/1005008529231123.html?spm=a2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"
"Battery protection","DW01A","1","2.54","https://www.aliexpress.com/item/1005008626342372.html?spm=a2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"
"Capacitor Tantalum SMD","100uF 3528-12 (Metric)","1","4.05","https://my.mouser.com/en/ProductDetail/Vishay-Sprague/293D10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"
"Capacitor Tantalum SMD","10uF 0603","4","9.68","https://www.aliexpress.com/item/1005003344584575.html?spm=a2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"
"Push button switch","SW-SMD_TC-1101V-C-B-W","1","0.40","https://item.szlcsc.com/300030.html"
"Push button switch SMD","SW_SPST_B3U-1000P","2","1.46","https://www.aliexpress.com/item/1005009548875400.html?spm=a2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"
"Ceramic resistor SMD","10k 0805","13","1.99","https://www.aliexpress.com/item/1005007183002569.html?spm=a2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"
"Ceramic resistor SMD","2k 0603","1","1.80","https://www.aliexpress.com/item/1005003529112557.html?spm=a2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"
"Ceramic resistor SMD","82k 0805","1","2.03","https://www.aliexpress.com/item/1005007183002569.html?spm=a2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"
"Ceramic resistor SMD","100 0402","1","1.38","https://www.aliexpress.com/item/1005003721873929.html?spm=a2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"
"Ceramic resistor SMD","3.9k 0402","4","1.38","https://www.aliexpress.com/item/1005003721873929.html?spm=a2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"
"Ceramic resistor SMD","1m 0603","1","1.48","https://www.aliexpress.com/item/1005010109041806.html?spm=a2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"
"Ceramic resistor SMD","5k1 0603","2","1.75","https://www.aliexpress.com/item/1005003529112557.html?spm=a2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"
"Ceramic resistor SMD","1k 0402","1","1.38","https://www.aliexpress.com/item/1005003721873929.html?spm=a2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"
"Ceramic resistor SMD","100k 0805","6","2.00","https://www.aliexpress.com/item/1005007183002569.html?spm=a2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"
"Ceramic resistor SMD","4.7k 0805","1","2.00","https://www.aliexpress.com/item/1005007183002569.html?spm=a2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"
"Ceramic resistor SMD","470 0603","2","1.80","https://www.aliexpress.com/item/1005003529112557.html?spm=a2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"
"Ceramic resistor SMD","43k 0805","1","2.03","https://www.aliexpress.com/item/1005007183002569.html?spm=a2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"
"Ceramic resistor SMD","732k 0603","1","2.10","https://www.aliexpress.com/item/1005005459557840.html?spm=a2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"
"Rotary encoder with switch","EC11E","1","2.94","https://www.aliexpress.com/item/32976046900.html?spm=a2g0o.d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"
"Single-cell battery","755060 LiPo 3000mAh","1","8.90","https://www.aliexpress.com/item/1005006259194674.html?spm=a2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"
"Li-lon Battery Charger","TP4056","1","0.52","https://www.aliexpress.com/item/1005005487915175.html?spm=a2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"
"Thermistor","10k 0402","1","2.81","https://www.aliexpress.com/item/1005010466857933.html?spm=a2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"
"Ceramic capacitor SMD","100nF 0603","4","2.01","https://www.aliexpress.com/item/1005007660078779.html?spm=a2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"
"Ceramic capacitor SMD","10uF 0805","5","2.64","https://www.aliexpress.com/item/1005012364450156.html?spm=a2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"
"Ceramic capacitor SMD","1uF 0805","3","2.35","https://www.aliexpress.com/item/1005012364450156.html?spm=a2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"
"Ceramic capacitor SMD","10nF 0603","1","2.00","https://www.aliexpress.com/item/1005007660078779.html?spm=a2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"
"Ceramic capacitor SMD","22uF 0805","3","3.55","https://www.aliexpress.com/item/1005012364450156.html?spm=a2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"
"Ceramic capacitor SMD","0.1uF 0805","2","1.43","https://www.aliexpress.com/item/1005006142309480.html?spm=a2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"
"Ceramic capacitor SMD","100uF 0805","2","13.72","https://www.aliexpress.com/item/1005005590636993.html?spm=a2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"
"Ceramic capacitor SMD","0.1uF 0201","4","0.95","https://www.aliexpress.com/item/1005008499718166.html?spm=a2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"
"Ceramic capacitor SMD","2.2uF 0603","2","2.03","https://www.aliexpress.com/item/1005007660078779.html?spm=a2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"
"Ceramic capacitor SMD","1nF 0603","1","1.98","https://www.aliexpress.com/item/1005007660078779.html?spm=a2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"
"Ceramic capacitor SMD","2.2nF 0805","2","3.04","https://www.aliexpress.com/item/33039604868.html?spm=a2g0o.p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"
"Ceramic capacitor SMD","100pF 0603","1","2.03","https://www.aliexpress.com/item/1005007660078779.html?spm=a2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"
"USBType-C Receptacle","USB4125-GF-A","1","0.60","https://www.digikey.my/en/products/detail/gct/USB4125-GF-A/13547388"
"AMOLED Display","1.73 inch 466x466 QSPI","1","7.47","https://item.taobao.com/item.htm?id=952177467095&mi_id=0000j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"
